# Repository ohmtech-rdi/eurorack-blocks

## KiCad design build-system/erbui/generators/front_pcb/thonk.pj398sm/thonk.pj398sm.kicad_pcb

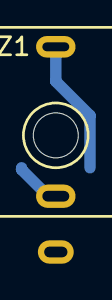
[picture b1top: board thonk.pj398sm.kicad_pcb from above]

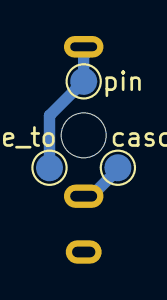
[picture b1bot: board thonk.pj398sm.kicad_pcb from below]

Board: 2 copper layers, 4 parts (3 on the bottom side), 2 nets.

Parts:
Cascade0: TestPoint; TestPoint_Pad_D1.5mm
Pin0: TestPoint; TestPoint_Pad_D1.5mm
ZZ1: IN; ThonkiconnJack
ZZ2: TestPoint; TestPoint_Pad_D1.5mm

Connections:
unnamed: Cascade0.1, ZZ1.TN
unnamed: Pin0.1, ZZ1.T, ZZ2.1
